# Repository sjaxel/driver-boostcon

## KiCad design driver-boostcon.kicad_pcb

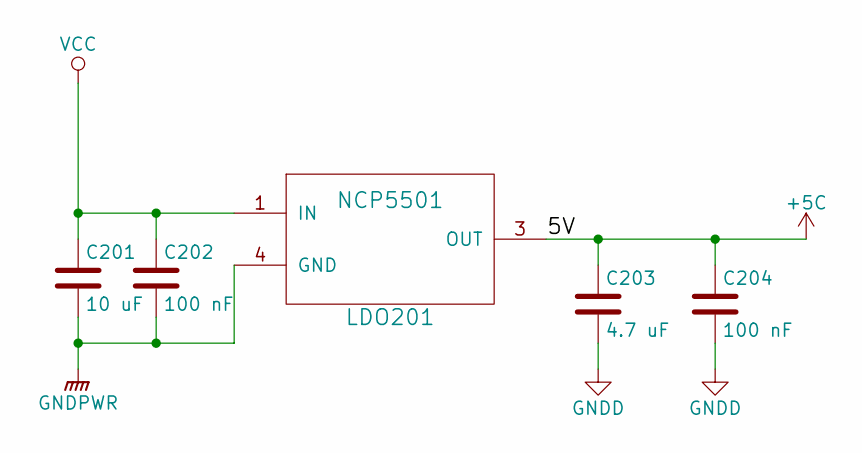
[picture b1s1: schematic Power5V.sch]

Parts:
C201: 10 uF; CP_Elec_6.3x5.3
C202: 100 nF; C_0603_CustomText
C203: 4.7 uF; C_0805_CustomText
C204: 100 nF; C_0805_CustomText
LDO201: NCP5501; TO-263-3Lead_TabPin4

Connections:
GNDPWR: C201.2, C202.2, LDO201.4 (GND); also elsewhere on the board
VCC: C201.1, C202.1, LDO201.1 (IN); also elsewhere on the board

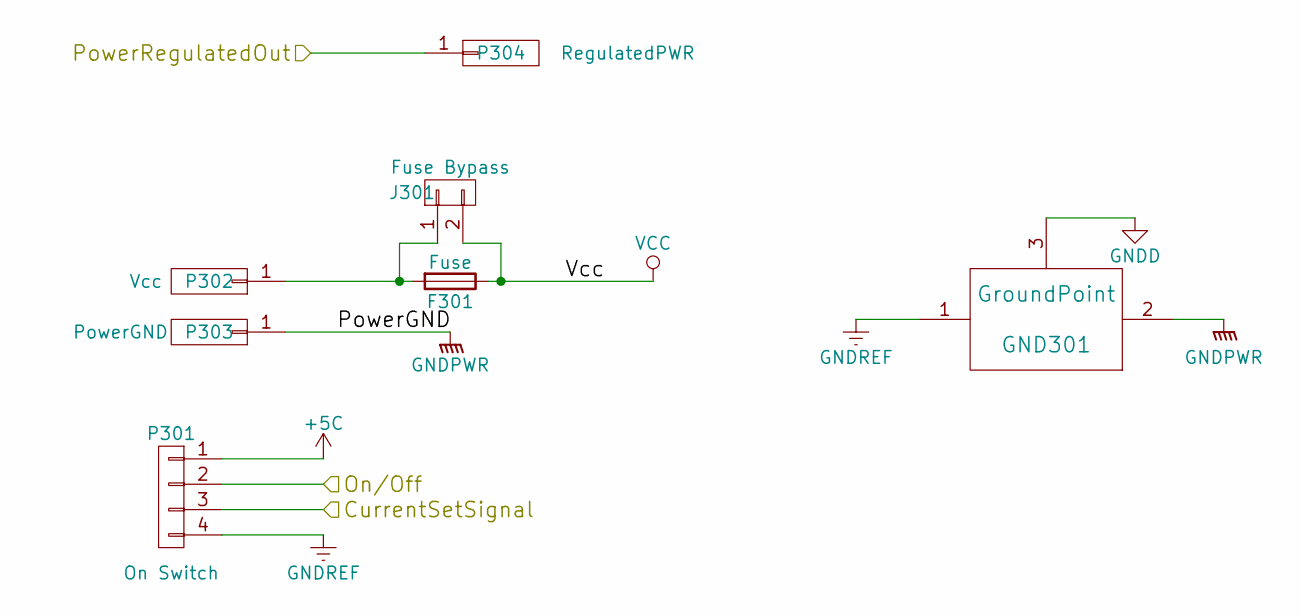
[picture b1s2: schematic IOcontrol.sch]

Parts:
F301: Fuse; Littlefuse_30mm_M5
GND301: GroundPoint; NetTie-II_Connected_SMD
J301: Fuse Bypass; Pin_Header_Angled_1x02_Pitch2.54mm
P301: On Switch; Socket_Strip_Straight_1x04_Pitch2.54mm
P302: Vcc; MountingHole_3.2mm_M3_Pad
P303: PowerGND; MountingHole_3.2mm_M3_Pad
P304: RegulatedPWR; MountingHole_3.2mm_M3_Pad

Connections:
/Current Set/CurrentSetInput: P301.3; also elsewhere on the board
/CurrentSense/CurrentSignal-: P304.1; also elsewhere on the board
/MCU/On/Off: P301.2; also elsewhere on the board
GNDPWR: GND301.2, P303.1; also elsewhere on the board
GNDREF: GND301.1, P301.4; also elsewhere on the board
unnamed: F301.2, J301.1, P302.1
VCC: F301.1, J301.2; also elsewhere on the board

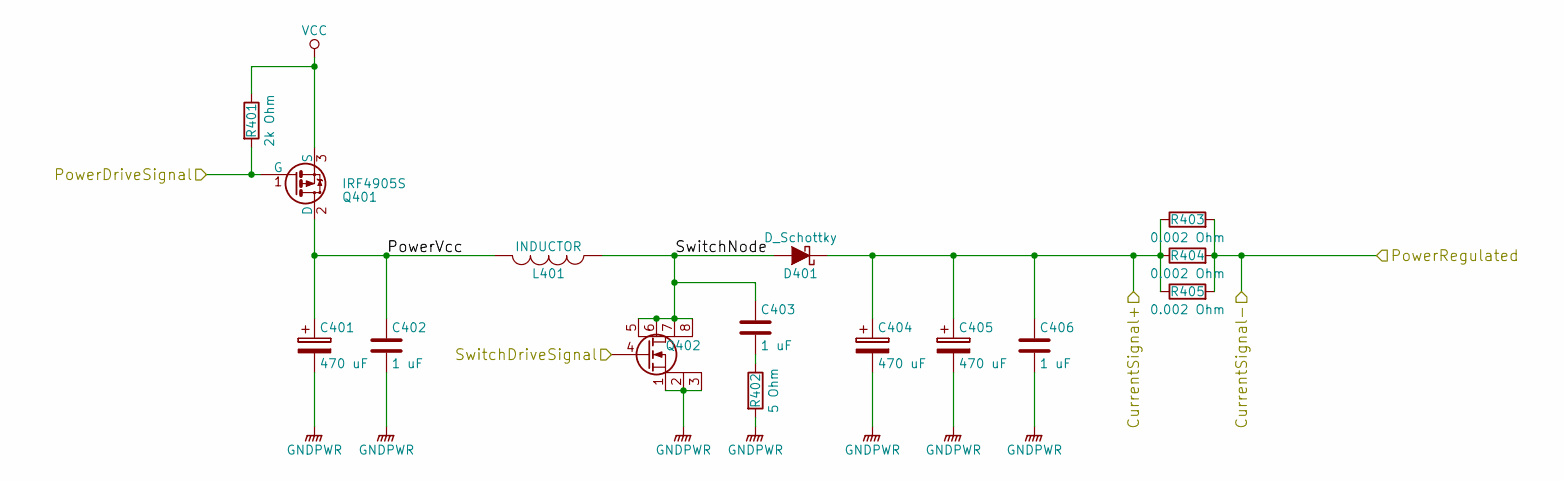
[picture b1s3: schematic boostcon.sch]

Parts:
C401, C404, C405: 470 uF; CP_Elec_10x10.5
C402, C403, C406: 1 uF; C_0805_CustomText
D401: D_Schottky; TO-220AB
L401: INDUCTOR; SER2900
Q401: IRF4905S; TO-263-3Lead_NoPin2
Q402: BSC016N04LS; PG-TDSON-8
R401: 2k Ohm; C_0603_CustomText
R402: 5 Ohm; C_0603_CustomText
R403, R404, R405: 0.002 Ohm; R-SMD-4527

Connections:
/CurrentSense/CurrentSignal+: C404.1, C405.1, C406.1, D401.1 (K), R403.1, R404.1, R405.1; also elsewhere on the board
/CurrentSense/CurrentSignal-: R403.2, R404.2, R405.2; also elsewhere on the board
/MosFET driver/PowerDriveSignal: Q401.1 (G), R401.2; also elsewhere on the board
/MosFET driver/SwitchDriveSignal: Q402.4 (G); also elsewhere on the board
/Power stage/PowerVcc: C401.1, C402.1, L401.2, Q401.2 (D)
/Power stage/SwitchNode: C403.1, D401.2 (A), L401.1, Q402.5 (D), Q402.6 (D), Q402.7 (D), Q402.8 (D)
GNDPWR: C401.2, C402.2, C404.2, C405.2, C406.2, Q402.1 (S), Q402.2 (S), Q402.3 (S), R402.2; also elsewhere on the board
unnamed: C403.2, R402.1
VCC: Q401.3 (S), R401.1; also elsewhere on the board

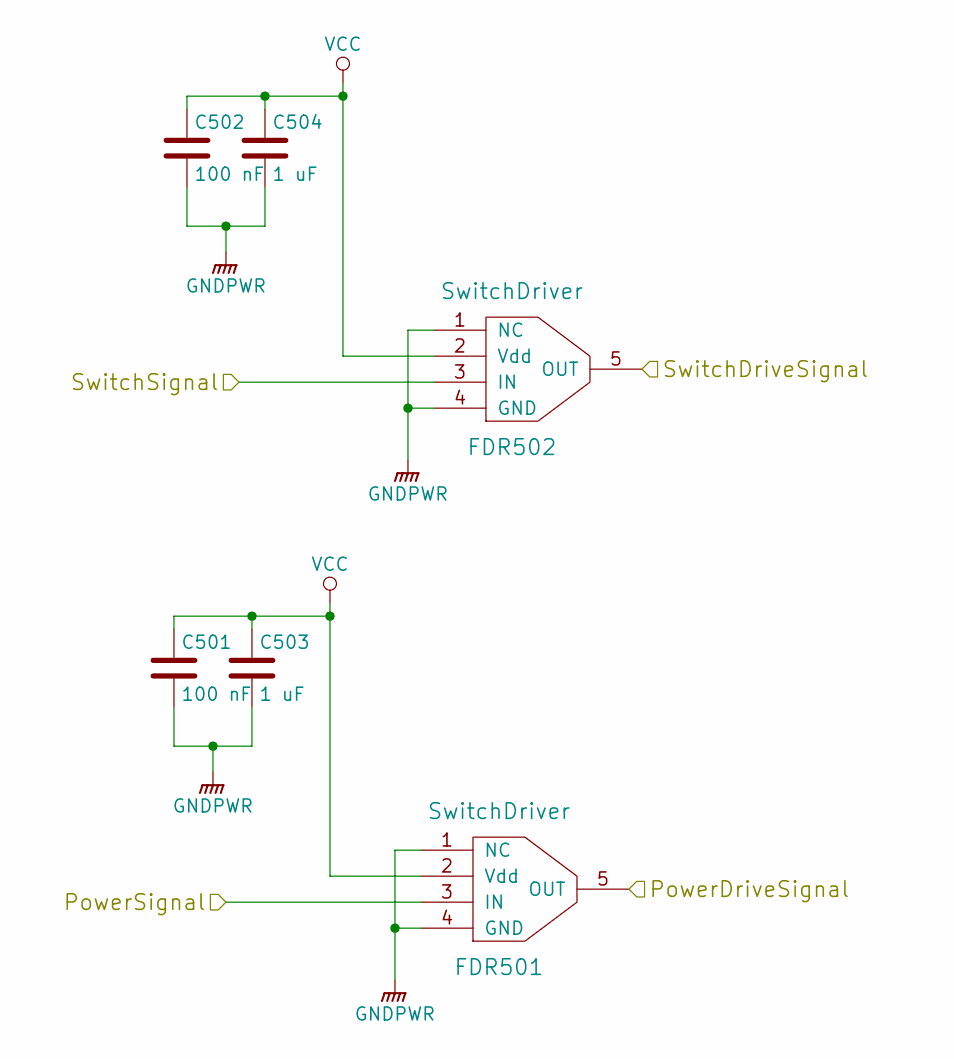
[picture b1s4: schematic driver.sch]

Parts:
C501, C502: 100 nF; C_0603_CustomText
C503, C504: 1 uF; C_0805_CustomText
FDR501, FDR502: SwitchDriver; SOT-23-5

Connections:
/MCU/GateDriveSignal: FDR502.3 (IN); also elsewhere on the board
/MCU/PowerDriveSignal: FDR501.3 (IN); also elsewhere on the board
/MosFET driver/PowerDriveSignal: FDR501.5 (OUT); also elsewhere on the board
/MosFET driver/SwitchDriveSignal: FDR502.5 (OUT); also elsewhere on the board
GNDPWR: C501.2, C502.2, C503.2, C504.2, FDR501.1 (NC), FDR501.4 (GND), FDR502.1 (NC), FDR502.4 (GND); also elsewhere on the board
VCC: C501.1, C502.1, C503.1, C504.1, FDR501.2 (Vdd), FDR502.2 (Vdd); also elsewhere on the board

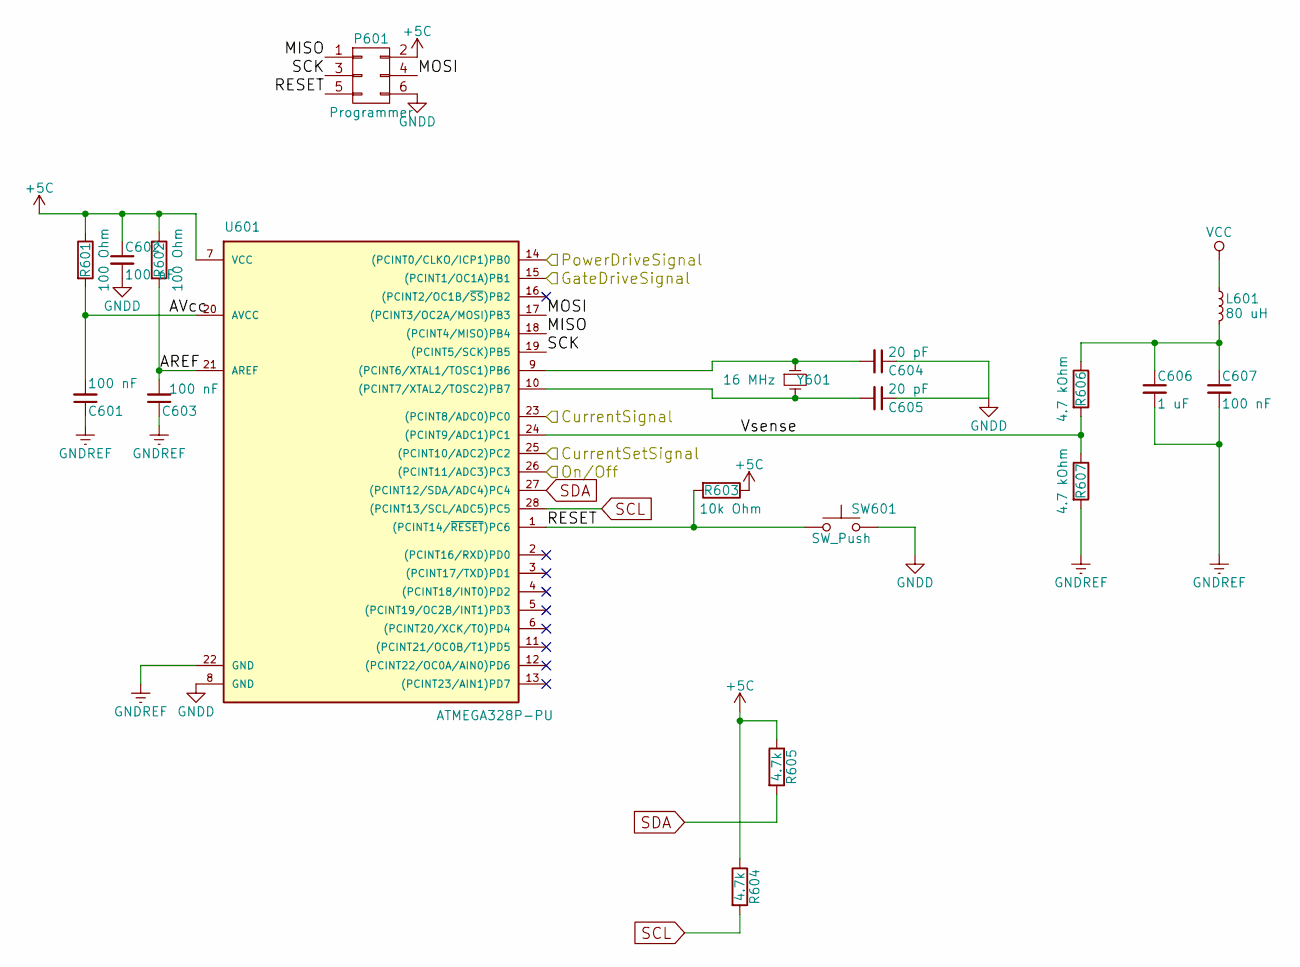
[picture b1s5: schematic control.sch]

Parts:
C601, C602, C603, C607: 100 nF; C_0603_CustomText
C604, C605: 20 pF; C_0603_CustomText
C606: 1 uF; C_0805_CustomText
L601: 80 uH; Chipdrossel
P601: Programmer; Pin_Header_Straight_2x03_Pitch2.54mm
R601, R602: 100 Ohm; C_0603_CustomText
R603: 10k Ohm; C_0603_CustomText
R604, R605: 4.7k; C_0603_CustomText
R606, R607: 4.7 kOhm; C_0603_CustomText
SW601: SW_Push; Button_SMD_6x6mm
U601: ATMEGA328P-PU; DIP-28_W7.62mm_Socket
Y601: 16 MHz; Crystal_SMD_4.6mmx11.2mm

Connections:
/Current Set/CurrentSetFiltered: U601.25 ((PCINT10/ADC2)PC2); also elsewhere on the board
/CurrentSense/CurrentSignal: U601.23 ((PCINT8/ADC0)PC0); also elsewhere on the board
/MCU/AREF: C603.2, R602.2, U601.21 (AREF)
/MCU/AVcc: C601.2, R601.2, U601.20 (AVCC)
/MCU/GateDriveSignal: U601.15 ((PCINT1/OC1A)PB1); also elsewhere on the board
/MCU/MISO: P601.1, U601.18 ((PCINT4/MISO)PB4)
/MCU/MOSI: P601.4, U601.17 ((PCINT3/OC2A/MOSI)PB3)
/MCU/On/Off: U601.26 ((PCINT11/ADC3)PC3); also elsewhere on the board
/MCU/PowerDriveSignal: U601.14 ((PCINT0/CLKO/ICP1)PB0); also elsewhere on the board
/MCU/RESET: P601.5, R603.2, SW601.1, U601.1 ((PCINT14/~RESET~)PC6)
/MCU/SCK: P601.3, U601.19 ((PCINT5/SCK)PB5)
/MCU/Vsense: R606.2, R607.1, U601.24 ((PCINT9/ADC1)PC1)
GNDREF: C601.1, C603.1, C606.2, C607.2, R607.2, U601.22 (GND); also elsewhere on the board
unnamed: C604.2, U601.9 ((PCINT6/XTAL1/TOSC1)PB6), Y601.1
unnamed: C605.2, U601.10 ((PCINT7/XTAL2/TOSC2)PB7), Y601.2
unnamed: C606.1, C607.1, L601.2, R606.1
SCL: R604.2, U601.28 ((PCINT13/SCL/ADC5)PC5); also elsewhere on the board
SDA: R605.2, U601.27 ((PCINT12/SDA/ADC4)PC4); also elsewhere on the board
VCC: L601.1; also elsewhere on the board

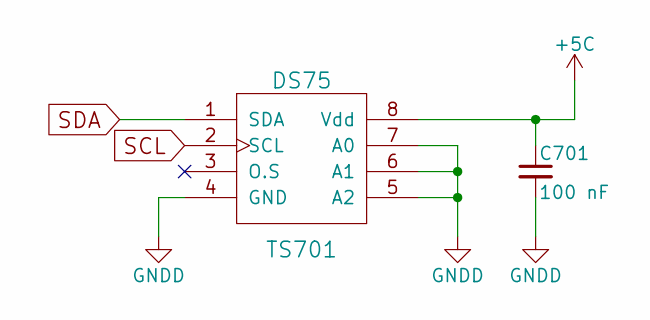
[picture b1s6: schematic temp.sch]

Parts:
C701: 100 nF; C_0603_CustomText
TS701: DS75; SOIC-8_3.9x4.9mm_Pitch1.27mm

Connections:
SCL: TS701.2 (SCL); also elsewhere on the board
SDA: TS701.1 (SDA); also elsewhere on the board

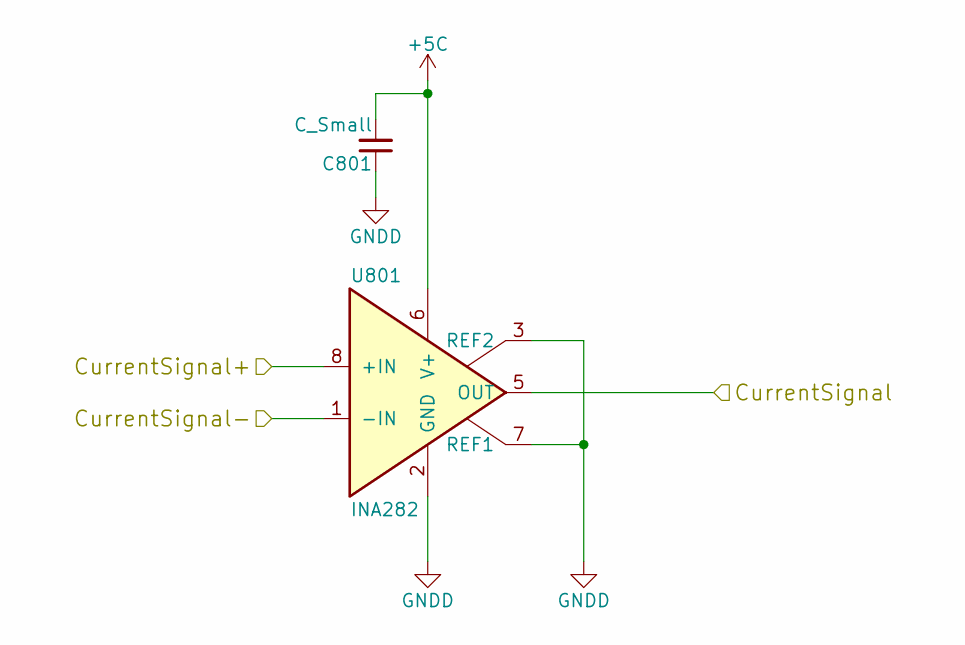
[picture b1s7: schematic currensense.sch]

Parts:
C801: C_Small; C_0603_CustomText
U801: INA282; SOIC-8_3.9x4.9mm_Pitch1.27mm

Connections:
/CurrentSense/CurrentSignal+: U801.8 (+IN); also elsewhere on the board
/CurrentSense/CurrentSignal-: U801.1 (-IN); also elsewhere on the board
unnamed 27: U801.5 (OUT); also elsewhere on the board

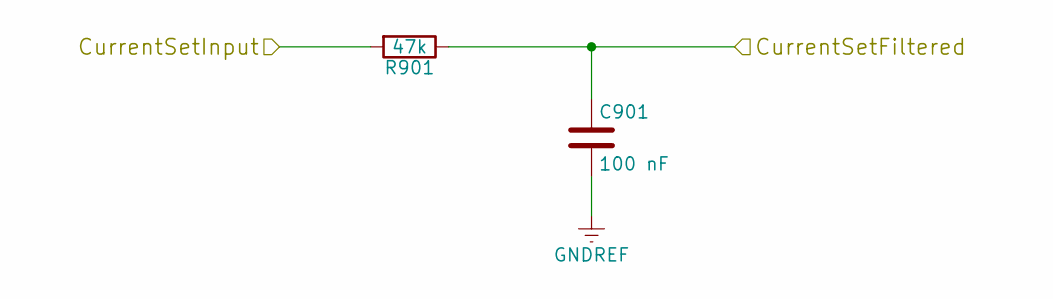
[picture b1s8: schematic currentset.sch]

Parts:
C901: 100 nF; C_0603_CustomText
R901: 47k; C_0603_CustomText

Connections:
/Current Set/CurrentSetFiltered: C901.1, R901.1; also elsewhere on the board
/Current Set/CurrentSetInput: R901.2; also elsewhere on the board
GNDREF: C901.2; also elsewhere on the board

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
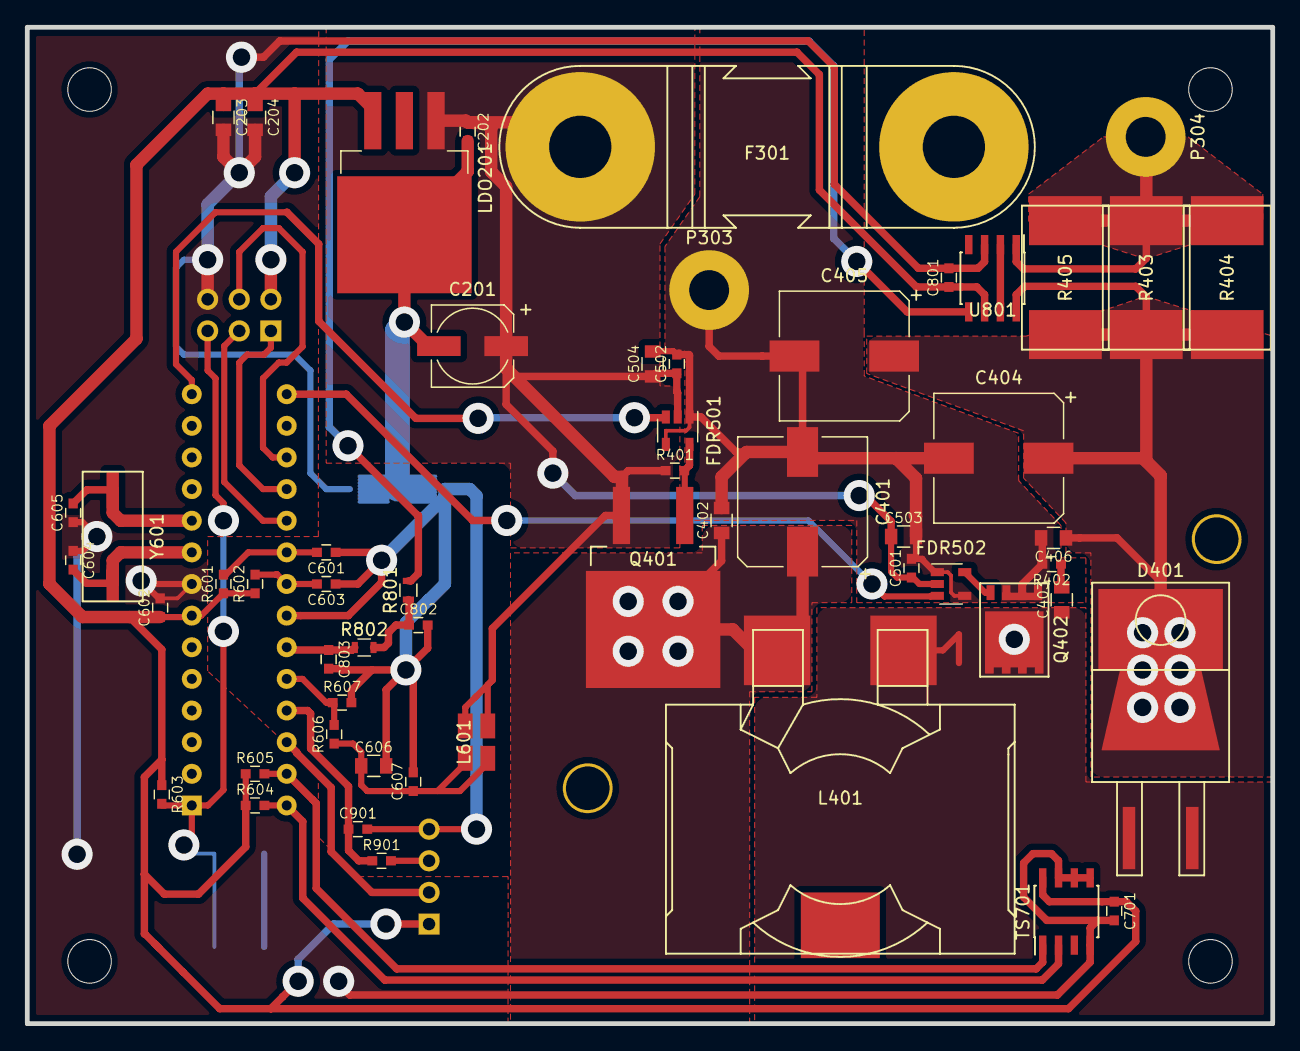
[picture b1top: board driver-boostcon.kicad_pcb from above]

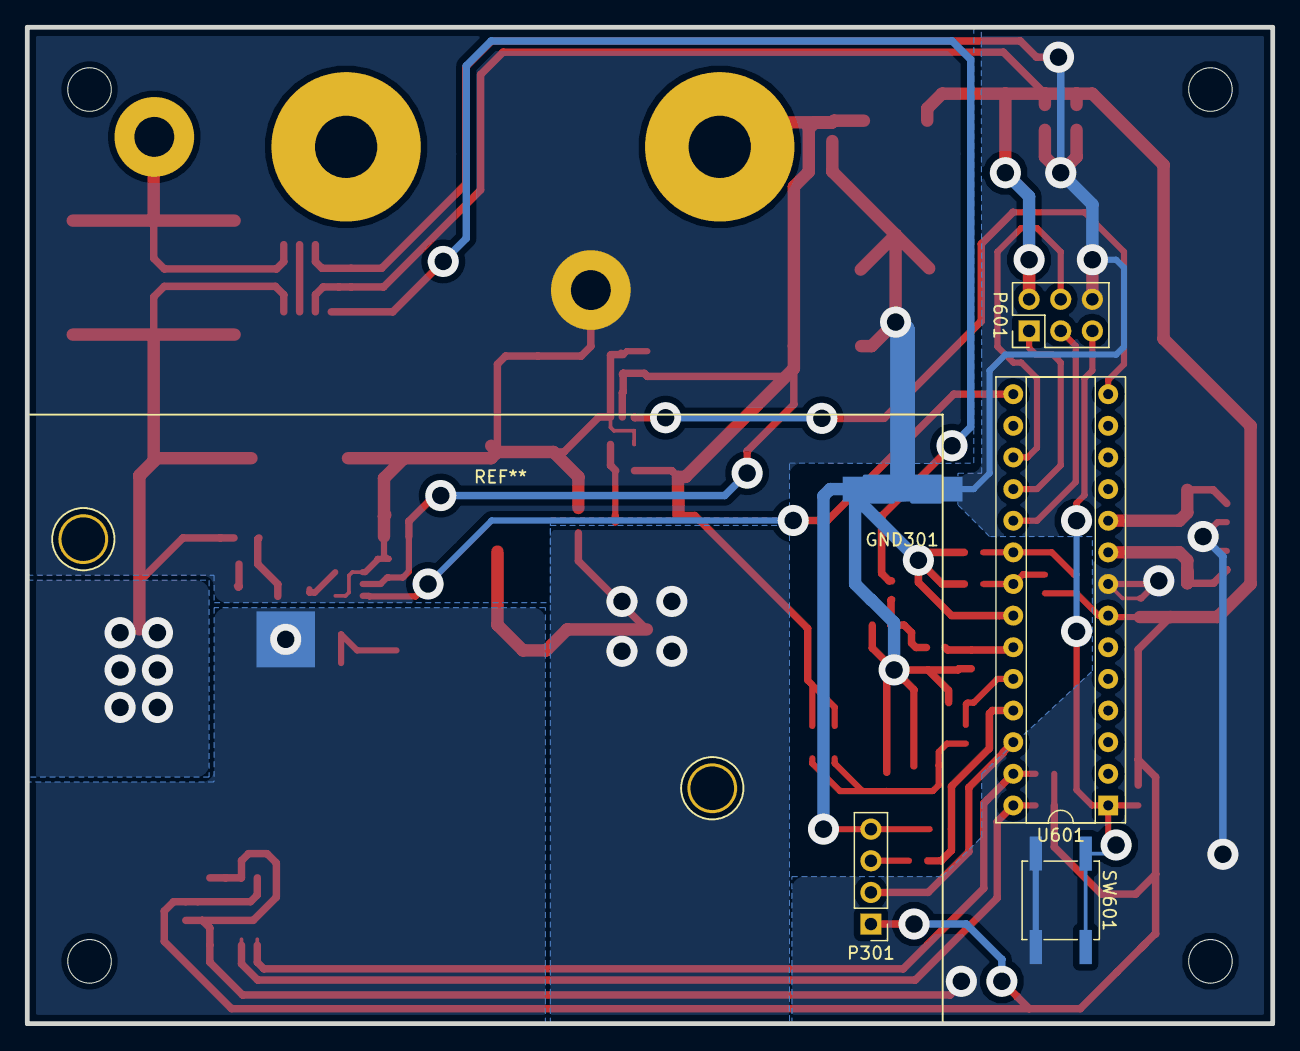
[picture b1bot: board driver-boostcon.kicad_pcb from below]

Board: 2 copper layers, 100.0 x 80.0 mm, 60 parts (5 on the bottom side), 32 nets.

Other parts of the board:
C802, C803: 680 nF; C_0603_CustomText
R801, R802: 6k; R_0603_CustomText

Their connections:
/CurrentSense/CurrentSignal: C803.1, R802.1; also elsewhere on the board
GNDREF: C802.2, C803.2; also elsewhere on the board
unnamed: C802.1, R801.1, R802.2
unnamed 27: R801.2; also elsewhere on the board

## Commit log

2017-04-21 Added everything so far
2017-04-22 Separated digital and power sections more
2017-04-23 Resolved library issues
2017-05-02 Syncing
2017-06-03 New amplifiers, fuse and general mayhem
2017-06-03 Reworked layout and added heatsink.
2017-06-05 Added power traces and corrected diode polarity
